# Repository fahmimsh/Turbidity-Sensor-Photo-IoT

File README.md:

Project Turbidity Sensor With Sensor LDR photo Dioda, Photo Transistor, Base IoT link Youtube https://www.youtube.com/watch?v=5ldWMMYThlE

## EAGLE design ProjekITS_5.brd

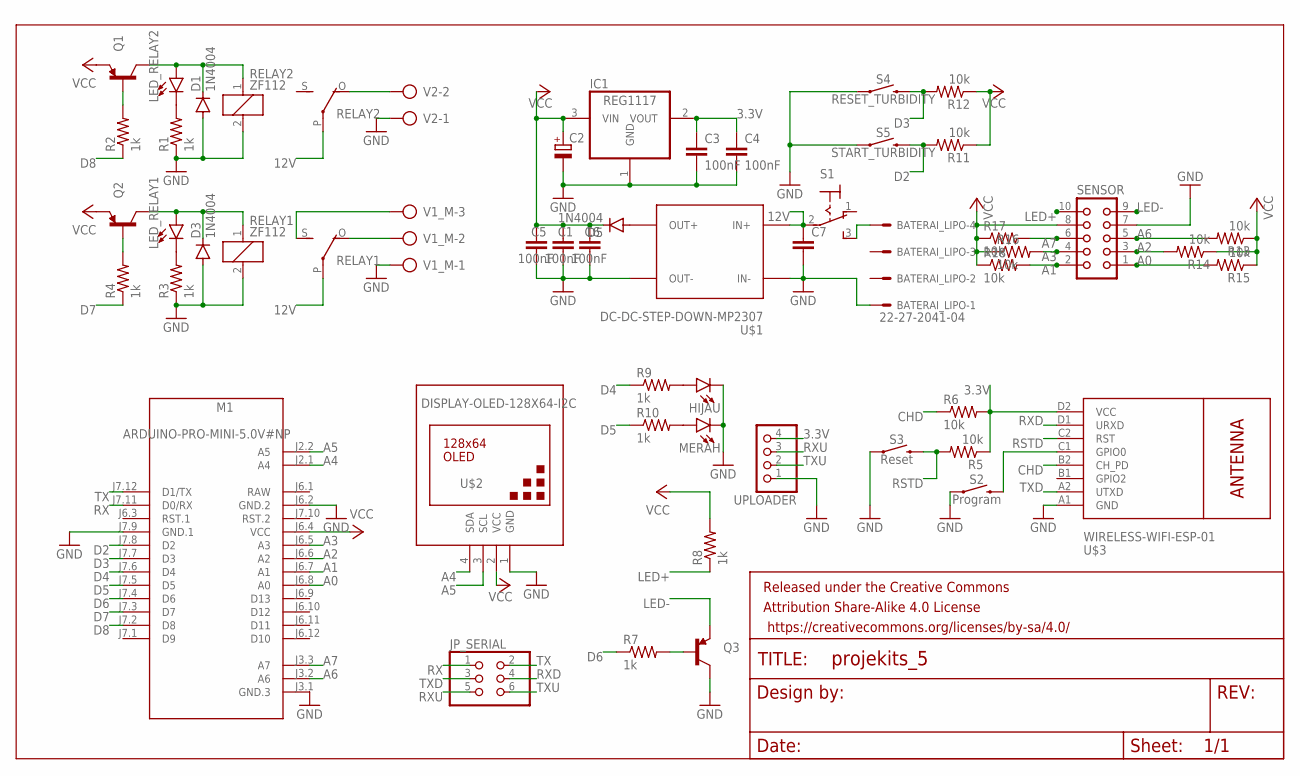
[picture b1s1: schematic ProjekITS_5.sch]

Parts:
BATERAI_LIPO: 22-27-2041-04; 6410-04
C1, C3, C4, C5, C6: 100nF; C0805K
C2: CPOL-EUCT3528; CT3528
C7: C-EU050-030X075; C050-030X075
D1, D3, D5: 1N4004; DO41-10
FRAME1: FRAME-LETTER; CREATIVE_COMMONS
HIJAU: LED5MM; LED_5MM
IC1: REG1117; SOT223
JP_SERIAL: PINHD-2X3; 2X03
LED_RELAY1, LED_RELAY2: LED3MM; LED_3MM
M1: ARDUINO-PRO-MINI-5.0V#NP; ARDUINO-PRO-MINI#NP
MERAH: LED5MM; LED_5MM
Q1, Q2, Q3: TRANSISTOR_PNPSMD; SOT23-3
R1, R2, R3, R4, R7, R8, R9, R10: 1k; R0805
R5, R6, R11, R12, R13, R14, R15, R16, R17, R18: 10k; R0805
RELAY1, RELAY2: ZF112
S1: 320-916
S2: Program; TACTILE_SWITCH_PTH_6.0MM
S3: Reset; TACTILE_SWITCH_PTH_6.0MM
S4: RESET_TURBIDITY; TACTILE_SWITCH_PTH_6.0MM
S5: START_TURBIDITY; TACTILE_SWITCH_PTH_6.0MM
SENSOR: CON10L
U$1: DC-DC-STEP-DOWN-MP2307
U$2: DISPLAY-OLED-128X64-I2C
U$3: WIRELESS-WIFI-ESP-01
UPLOADER: PINHD-1X4/90; 1X04/90
V1_M: AK500/3
V2: AK500/2

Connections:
3.3V: C3.1, C4.1, IC1.2 (VOUT), R5.1, R6.2, U$3.D2 (VCC), UPLOADER.4
12V: C7.1, RELAY1.P, RELAY2.P, S1.2, U$1.IN+
A0: M1.J6.8 (A0), R15.2, SENSOR.1
A1: M1.J6.7 (A1), R18.2, SENSOR.2
A2: M1.J6.6 (A2), R14.2, SENSOR.3
A3: M1.J6.5 (A3), R16.2, SENSOR.4
A4: M1.J2.1 (A4), U$2.4 (SDA)
A5: M1.J2.2 (A5), U$2.3 (SCL)
A6: M1.J3.2 (A6), R13.2, SENSOR.5
A7: M1.J3.3 (A7), R17.2, SENSOR.6
CHD: R6.1, U$3.B2 (CH_PD)
D2: M1.J7.8 (D2), R11.2, S5.3 (2)
D3: M1.J7.7 (D3), R12.2, S4.3 (2)
D4: M1.J7.6 (D4), R9.1
D5: M1.J7.5 (D5), R10.1
D6: M1.J7.4 (D6), R7.1
D7: M1.J7.3 (D7), R4.1
D8: M1.J7.2 (D8), R2.1
GND: BATERAI_LIPO.1, C1.2, C2.-, C3.2, C4.2, C5.2, C6.2, C7.2, D1.A, D3.A, HIJAU.K (C), IC1.1 (GND), M1.J3.1 (GND.3), M1.J6.2 (GND.2), M1.J7.9 (GND.1), MERAH.K (C), Q3.3 (C), R1.1, R3.1, RELAY1.2, RELAY2.2, S2.1, S3.1, S4.1, S5.1, SENSOR.7, U$1.IN-, U$1.OUT-, U$2.1 (GND), U$3.A1 (GND), UPLOADER.1, V1_M.1, V2.1
LED+: R8.1, SENSOR.10
LED-: Q3.2 (E), SENSOR.9
unnamed: D1.C, LED_RELAY2.A, Q1.3 (C), RELAY2.1
unnamed: HIJAU.A, R9.2
unnamed: D5.A, U$1.OUT+
unnamed: LED_RELAY2.K (C), R1.2
unnamed: Q1.1 (B), R2.2
unnamed: D3.C, LED_RELAY1.A, Q2.3 (C), RELAY1.1
unnamed: LED_RELAY1.K (C), R3.2
unnamed: Q2.1 (B), R4.2
unnamed: RELAY2.O, V2.2
unnamed: RELAY1.S, V1_M.3
unnamed: RELAY1.O, V1_M.2
unnamed: MERAH.A, R10.2
unnamed: BATERAI_LIPO.4, S1.3 (S)
unnamed: Q3.1 (B), R7.2
unnamed: S2.3 (2), U$3.C1 (GPIO0)
RAW: M1.J6.1 (RAW)
RSTD: R5.2, S3.3 (2), U$3.C2 (RST)
RX: JP_SERIAL.1, M1.J7.11 (D0/RX)
RXD: JP_SERIAL.4, U$3.D1 (URXD)
RXU: JP_SERIAL.5, UPLOADER.3
TX: JP_SERIAL.2, M1.J7.12 (D1/TX)
TXD: JP_SERIAL.3, U$3.A2 (UTXD)
TXU: JP_SERIAL.6, UPLOADER.2
VCC: C1.1, C2.+, C5.1, C6.1, D5.C, IC1.3 (VIN), M1.J6.4 (VCC), Q1.2 (E), Q2.2 (E), R8.2, R11.1, R12.1, R13.1, R14.1, R15.1, R16.1, R17.1, R18.1, SENSOR.8, U$2.2 (VCC)

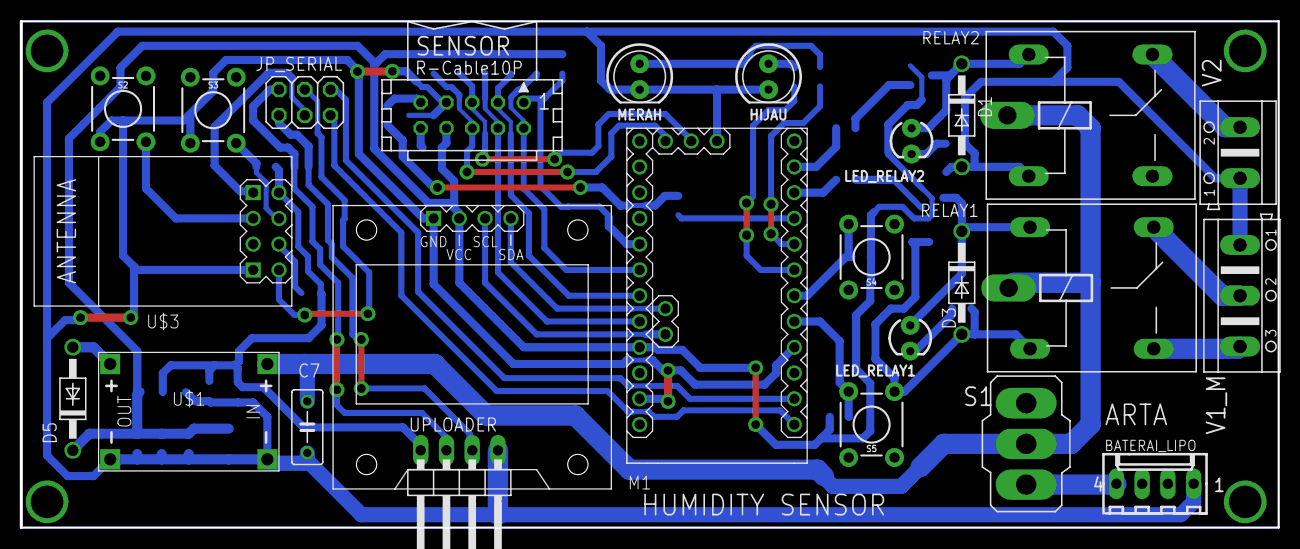
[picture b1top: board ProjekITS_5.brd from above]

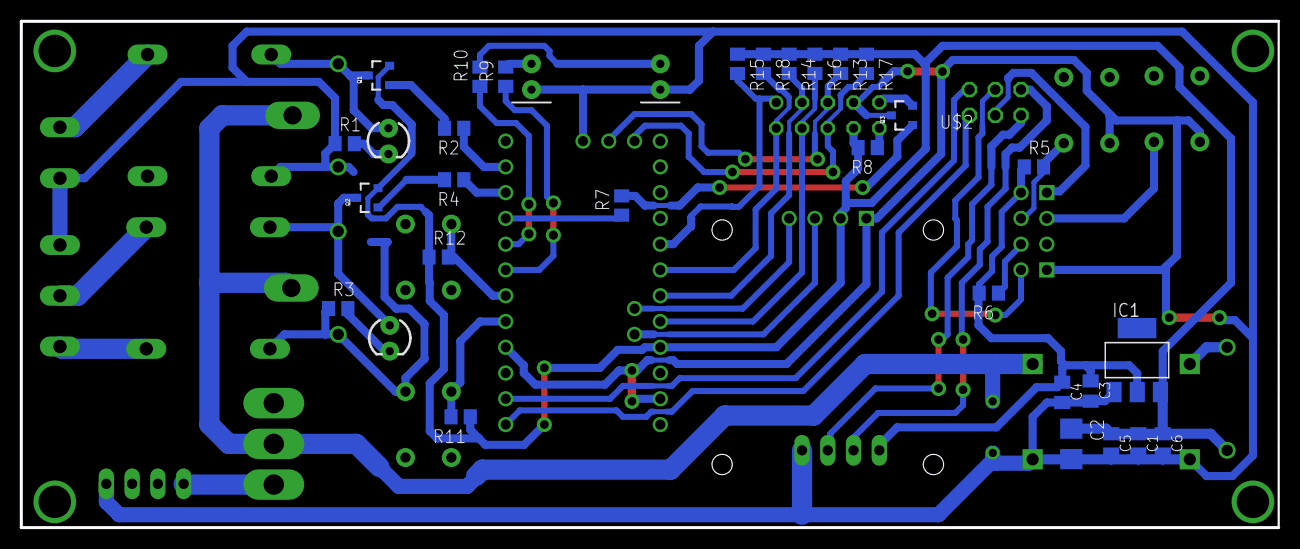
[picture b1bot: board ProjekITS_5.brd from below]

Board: 2 copper layers, 124.0 x 49.9 mm, 54 parts (28 on the bottom side), 44 nets.

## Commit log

2021-04-06 Projek 4

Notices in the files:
parts and their libraries:
diy-modules: Released under the Creative Commons Attribution 4.0 International License: http://creativecommons.org/licenses/by/4.0
SparkFun-LED: Licensing: Creative Commons ShareAlike 4.0 International - https://creativecommons.org/licenses/by-sa/4.0
